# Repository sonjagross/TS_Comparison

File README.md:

# TS_Comparison
This repository includes all necessary code an description to build an experimental setup for the evaluation of tactile sensors.
- Overall description of the setup are provided in experimentalSetup/Bachelor_Thesis_ManuelKrummschmidt
- Necessary CAD files are provided in experimentalSetup/CADModels
- PCB and CAD Models of all Sensors are provided in sensorDesign/
- The code for the control of the robot setup is provided in code/RobotControl/
- A Tutorial on how to use the robot program code and include changes is provided in tutorials/

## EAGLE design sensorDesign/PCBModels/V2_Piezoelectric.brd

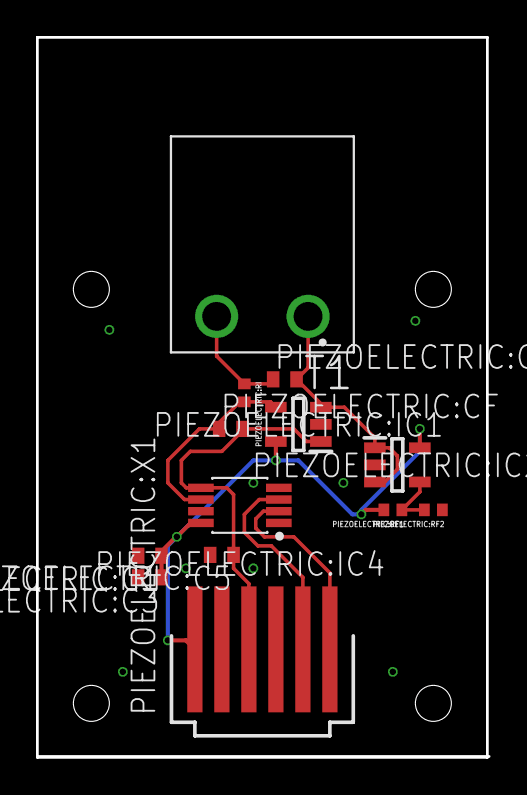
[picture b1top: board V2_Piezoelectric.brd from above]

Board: 2 copper layers, 25.0 x 40.0 mm, 13 parts (0 on the bottom side), 9 nets.

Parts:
PIEZOELECTRIC:C1, PIEZOELECTRIC:C5: GCM155R71C104JA55; C0402
PIEZOELECTRIC:C3: GCM155C7; C0402
PIEZOELECTRIC:CC: GCM155R71C104JA55; C0402
PIEZOELECTRIC:CF: GCM155R71C104JA55; C0402
PIEZOELECTRIC:IC1, PIEZOELECTRIC:IC2: TLV2771CDBVR; SOT95P280X145-5N
PIEZOELECTRIC:IC4: MCP4531-103E/MS; MSOP8
PIEZOELECTRIC:RF1, PIEZOELECTRIC:RF2: 10k; R0402
PIEZOELECTRIC:RI: 10k; R0402
PIEZOELECTRIC:X1: 87438-06
T1: 691312510002

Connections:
GND: PIEZOELECTRIC:C1.2, PIEZOELECTRIC:C3.2, PIEZOELECTRIC:C5.2, PIEZOELECTRIC:IC1.2, PIEZOELECTRIC:IC2.2, PIEZOELECTRIC:IC4.1, PIEZOELECTRIC:IC4.4, PIEZOELECTRIC:RF2.1, PIEZOELECTRIC:X1.2, PIEZOELECTRIC:X1.4
P+: PIEZOELECTRIC:CC.1, PIEZOELECTRIC:RI.1, T1.2
P-: PIEZOELECTRIC:CC.2, PIEZOELECTRIC:IC1.3, PIEZOELECTRIC:IC2.1, PIEZOELECTRIC:IC2.3, T1.1
PIEZOELECTRIC:IN-: PIEZOELECTRIC:CF.1, PIEZOELECTRIC:IC1.4, PIEZOELECTRIC:IC4.6, PIEZOELECTRIC:RI.2
PIEZOELECTRIC:N$3: PIEZOELECTRIC:IC2.4, PIEZOELECTRIC:RF1.1, PIEZOELECTRIC:RF2.2
PIEZOELECTRIC:OUT: PIEZOELECTRIC:C5.1, PIEZOELECTRIC:CF.2, PIEZOELECTRIC:IC1.1, PIEZOELECTRIC:IC4.5, PIEZOELECTRIC:X1.3
PIEZOELECTRIC:SCL: PIEZOELECTRIC:IC4.2, PIEZOELECTRIC:X1.6
PIEZOELECTRIC:SDA: PIEZOELECTRIC:IC4.3, PIEZOELECTRIC:X1.5
PIEZOELECTRIC:V+: PIEZOELECTRIC:C1.1, PIEZOELECTRIC:C3.1, PIEZOELECTRIC:IC1.5, PIEZOELECTRIC:IC2.5, PIEZOELECTRIC:IC4.8, PIEZOELECTRIC:RF1.2, PIEZOELECTRIC:X1.1

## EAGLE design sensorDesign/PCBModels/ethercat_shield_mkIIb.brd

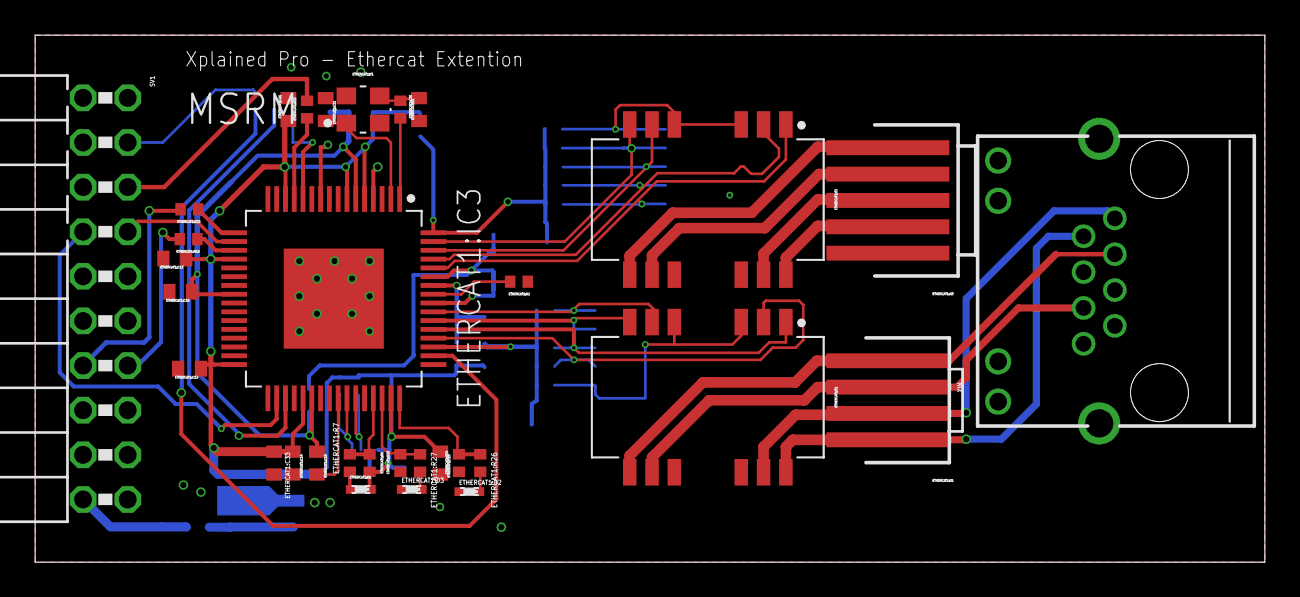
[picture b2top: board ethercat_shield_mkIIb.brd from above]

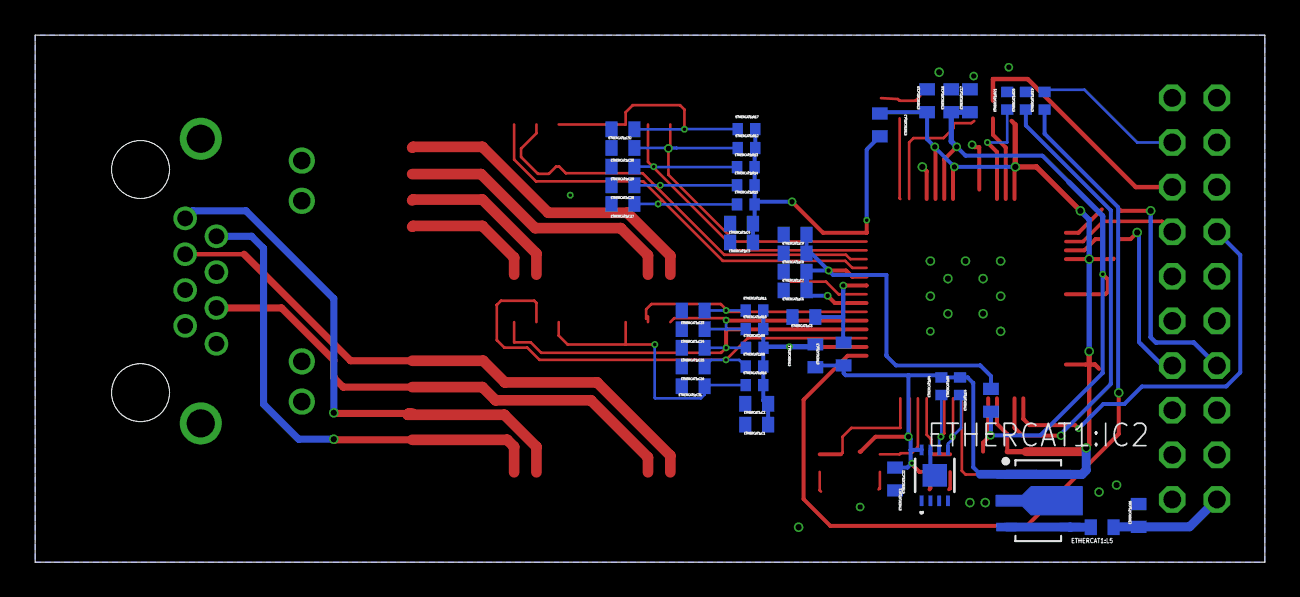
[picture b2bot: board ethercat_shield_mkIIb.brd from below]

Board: 2 copper layers, 70.0 x 30.0 mm, 78 parts (46 on the bottom side), 51 nets.

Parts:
ETHERCAT1:C1, ETHERCAT1:C3, ETHERCAT1:C6, ETHERCAT1:C8, ETHERCAT1:C16: 1u; C0402
ETHERCAT1:C2, ETHERCAT1:C4, ETHERCAT1:C5, ETHERCAT1:C7, ETHERCAT1:C9, ETHERCAT1:C10, ETHERCAT1:C11, ETHERCAT1:C12, ETHERCAT1:C13, ETHERCAT1:C14, ETHERCAT1:C15, ETHERCAT1:C18, ETHERCAT1:C19, ETHERCAT1:C22: 100n; C0402
ETHERCAT1:C17: 470p; C0402
ETHERCAT1:C20, ETHERCAT1:C21: 18p; C0402
ETHERCAT1:C23, ETHERCAT1:C24, ETHERCAT1:C25, ETHERCAT1:C26, ETHERCAT1:C27, ETHERCAT1:C28, ETHERCAT1:C29, ETHERCAT1:C30: GCM1555C1H100JA16; C0402
ETHERCAT1:C31, ETHERCAT1:C32: 22n; C0402
ETHERCAT1:C33: GRM155C80J106ME11D; C0402
ETHERCAT1:C66: 1uF; C0402
ETHERCAT1:D1, ETHERCAT1:D2, ETHERCAT1:D3: QBLP595-IG; LED0402
ETHERCAT1:IC1: CAT24C512IGT3HU5; UDFN8
ETHERCAT1:IC2: RP115H331B-T1-FE; SOT-89-5
ETHERCAT1:IC3: LAN9252/PT; TQFP64-T570
ETHERCAT1:L1, ETHERCAT1:L2, ETHERCAT1:L3, ETHERCAT1:L4, ETHERCAT1:L5: BLM15EG221SH1D; BEAD0402
ETHERCAT1:R1, ETHERCAT1:R16, ETHERCAT1:R17: 0R; R0402
ETHERCAT1:R2: 12k1; R0402
ETHERCAT1:R4, ETHERCAT1:R5: 4k7; R0402
ETHERCAT1:R6, ETHERCAT1:R24, ETHERCAT1:R25: 10k; R0402
ETHERCAT1:R7, ETHERCAT1:R26, ETHERCAT1:R27: RL0402FR-7W10KL; R0402
ETHERCAT1:R8, ETHERCAT1:R9, ETHERCAT1:R10, ETHERCAT1:R11, ETHERCAT1:R12, ETHERCAT1:R13, ETHERCAT1:R14, ETHERCAT1:R15: 49R9; R0402
ETHERCAT1:R18, ETHERCAT1:R19, ETHERCAT1:R20, ETHERCAT1:R21, ETHERCAT1:R22, ETHERCAT1:R23: 100; R0402
ETHERCAT1:T1, ETHERCAT1:T2: 749020100; SOIC127P965X533-16-TRAFO
ETHERCAT1:X1: 87438-0443; 87438-04
ETHERCAT1:X3: 87438-0543; 87438-05
ETHERCAT1:Y1: ECX-2236
SV1: FE10-2W
XIN: ATJ34L; J1

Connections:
+5V: ETHERCAT1:C66.1, ETHERCAT1:L5.1, SV1.20
ECAT_CS: ETHERCAT1:R19.2, SV1.3
ECAT_MISO: ETHERCAT1:R22.2, SV1.5
ECAT_MOSI: ETHERCAT1:R23.2, SV1.14
ECAT_SCK: ETHERCAT1:R18.2, SV1.13
ETHERCAT1:#MISO: ETHERCAT1:IC3.13, ETHERCAT1:R22.1
ETHERCAT1:#MOSI: ETHERCAT1:IC3.17, ETHERCAT1:R23.1
ETHERCAT1:#SCK: ETHERCAT1:IC3.19, ETHERCAT1:R18.1
ETHERCAT1:#SCS#: ETHERCAT1:IC3.50, ETHERCAT1:R19.1
ETHERCAT1:#SQI2: ETHERCAT1:IC3.12, ETHERCAT1:R21.1
ETHERCAT1:#SQI3: ETHERCAT1:IC3.35, ETHERCAT1:R20.1
ETHERCAT1:+3V3: ETHERCAT1:C10.1, ETHERCAT1:C11.1, ETHERCAT1:C12.1, ETHERCAT1:C13.1, ETHERCAT1:C14.1, ETHERCAT1:C15.1, ETHERCAT1:C22.1, ETHERCAT1:C33.1, ETHERCAT1:D1.2, ETHERCAT1:IC1.8, ETHERCAT1:IC2.1, ETHERCAT1:IC2.5, ETHERCAT1:IC3.5, ETHERCAT1:IC3.7, ETHERCAT1:IC3.14, ETHERCAT1:IC3.20, ETHERCAT1:IC3.32, ETHERCAT1:IC3.37, ETHERCAT1:IC3.47, ETHERCAT1:L1.1, ETHERCAT1:L2.1, ETHERCAT1:L3.1, ETHERCAT1:R4.2, ETHERCAT1:R5.2, ETHERCAT1:R6.2
ETHERCAT1:CT1: ETHERCAT1:C31.1, ETHERCAT1:R16.1, ETHERCAT1:T1.3, ETHERCAT1:T1.6
ETHERCAT1:CT2: ETHERCAT1:C32.1, ETHERCAT1:R17.1, ETHERCAT1:T2.3, ETHERCAT1:T2.6
ETHERCAT1:GPIO0: ETHERCAT1:IC3.48, ETHERCAT1:R24.2, ETHERCAT1:R26.1
ETHERCAT1:GPIO1: ETHERCAT1:IC3.46, ETHERCAT1:R25.2, ETHERCAT1:R27.1
ETHERCAT1:GPIO2: ETHERCAT1:IC3.45, ETHERCAT1:R6.1, ETHERCAT1:R7.2
ETHERCAT1:I2C_SCL: ETHERCAT1:IC1.6, ETHERCAT1:IC3.43, ETHERCAT1:R4.1
ETHERCAT1:I2C_SDA: ETHERCAT1:IC1.5, ETHERCAT1:IC3.42, ETHERCAT1:R5.1
ETHERCAT1:N$1: ETHERCAT1:D2.2, ETHERCAT1:R26.2
ETHERCAT1:N$2: ETHERCAT1:D3.2, ETHERCAT1:R27.2
ETHERCAT1:N$3: ETHERCAT1:IC2.3, ETHERCAT1:IC2.4, ETHERCAT1:L5.2
ETHERCAT1:N$15: ETHERCAT1:D1.1, ETHERCAT1:R7.1
ETHERCAT1:OSCI: ETHERCAT1:IC3.1, ETHERCAT1:R1.2
ETHERCAT1:OSCI1: ETHERCAT1:C20.2, ETHERCAT1:R1.1, ETHERCAT1:Y1.3
ETHERCAT1:OSCO: ETHERCAT1:C21.2, ETHERCAT1:IC3.2, ETHERCAT1:Y1.1
ETHERCAT1:OUT_RX_N: ETHERCAT1:T2.9, ETHERCAT1:X3.5
ETHERCAT1:OUT_RX_P: ETHERCAT1:T2.10, ETHERCAT1:X3.4
ETHERCAT1:OUT_TX_N: ETHERCAT1:T2.15, ETHERCAT1:X3.3
ETHERCAT1:OUT_TX_P: ETHERCAT1:T2.16, ETHERCAT1:X3.2
ETHERCAT1:RBIAS: ETHERCAT1:IC3.57, ETHERCAT1:R2.2
ETHERCAT1:RXA_N: ETHERCAT1:C24.1, ETHERCAT1:IC3.54, ETHERCAT1:R10.1, ETHERCAT1:T1.8
ETHERCAT1:RXA_P: ETHERCAT1:C23.1, ETHERCAT1:IC3.55, ETHERCAT1:R11.1, ETHERCAT1:T1.7
ETHERCAT1:RXB_N: ETHERCAT1:C28.1, ETHERCAT1:IC3.61, ETHERCAT1:R14.1, ETHERCAT1:T2.2
ETHERCAT1:RXB_P: ETHERCAT1:C27.1, ETHERCAT1:IC3.60, ETHERCAT1:R15.1, ETHERCAT1:T2.1
ETHERCAT1:TXA_N: ETHERCAT1:C26.1, ETHERCAT1:IC3.52, ETHERCAT1:R8.1, ETHERCAT1:T1.2
ETHERCAT1:TXA_P: ETHERCAT1:C25.1, ETHERCAT1:IC3.53, ETHERCAT1:R9.1, ETHERCAT1:T1.1
ETHERCAT1:TXB_N: ETHERCAT1:C30.1, ETHERCAT1:IC3.63, ETHERCAT1:R12.1, ETHERCAT1:T2.8
ETHERCAT1:TXB_P: ETHERCAT1:C29.1, ETHERCAT1:IC3.62, ETHERCAT1:R13.1, ETHERCAT1:T2.7
ETHERCAT1:VDD: ETHERCAT1:C16.1, ETHERCAT1:C17.1, ETHERCAT1:C18.1, ETHERCAT1:C19.1, ETHERCAT1:IC3.6, ETHERCAT1:IC3.24, ETHERCAT1:IC3.38, ETHERCAT1:L4.1
ETHERCAT1:VDD12TX: ETHERCAT1:C6.1, ETHERCAT1:C7.1, ETHERCAT1:C8.1, ETHERCAT1:C9.1, ETHERCAT1:IC3.56, ETHERCAT1:IC3.59, ETHERCAT1:L4.2
ETHERCAT1:VDD33BIAS: ETHERCAT1:C5.1, ETHERCAT1:IC3.58, ETHERCAT1:L3.2
ETHERCAT1:VDD33TXRX1: ETHERCAT1:C1.1, ETHERCAT1:C2.1, ETHERCAT1:IC3.51, ETHERCAT1:L1.2, ETHERCAT1:R8.2, ETHERCAT1:R9.2, ETHERCAT1:R10.2, ETHERCAT1:R11.2, ETHERCAT1:R16.2
ETHERCAT1:VDD33TXRX2: ETHERCAT1:C3.1, ETHERCAT1:C4.1, ETHERCAT1:IC3.64, ETHERCAT1:L2.2, ETHERCAT1:R12.2, ETHERCAT1:R13.2, ETHERCAT1:R14.2, ETHERCAT1:R15.2, ETHERCAT1:R17.2
GND: ETHERCAT1:C1.2, ETHERCAT1:C2.2, ETHERCAT1:C3.2, ETHERCAT1:C4.2, ETHERCAT1:C5.2, ETHERCAT1:C6.2, ETHERCAT1:C7.2, ETHERCAT1:C8.2, ETHERCAT1:C9.2, ETHERCAT1:C10.2, ETHERCAT1:C11.2, ETHERCAT1:C12.2, ETHERCAT1:C13.2, ETHERCAT1:C14.2, ETHERCAT1:C15.2, ETHERCAT1:C16.2, ETHERCAT1:C17.2, ETHERCAT1:C18.2, ETHERCAT1:C19.2, ETHERCAT1:C20.1, ETHERCAT1:C21.1, ETHERCAT1:C22.2, ETHERCAT1:C23.2, ETHERCAT1:C24.2, ETHERCAT1:C25.2, ETHERCAT1:C26.2, ETHERCAT1:C27.2, ETHERCAT1:C28.2, ETHERCAT1:C29.2, ETHERCAT1:C30.2, ETHERCAT1:C31.2, ETHERCAT1:C32.2, ETHERCAT1:C33.2, ETHERCAT1:C66.2, ETHERCAT1:D2.1, ETHERCAT1:D3.1, ETHERCAT1:IC1.1, ETHERCAT1:IC1.2, ETHERCAT1:IC1.3, ETHERCAT1:IC1.4, ETHERCAT1:IC1.7, ETHERCAT1:IC1.9, ETHERCAT1:IC2.2, ETHERCAT1:IC3.4, ETHERCAT1:IC3.8, ETHERCAT1:IC3.9, ETHERCAT1:IC3.10, ETHERCAT1:IC3.41, ETHERCAT1:IC3.65, ETHERCAT1:R2.1, ETHERCAT1:R24.1, ETHERCAT1:R25.1, ETHERCAT1:Y1.2, ETHERCAT1:Y1.4, SV1.2, SV1.19
RA_N: ETHERCAT1:T1.9, ETHERCAT1:X1.4, XIN.3
RA_P: ETHERCAT1:T1.10, ETHERCAT1:X1.3, XIN.6
SYNC0: ETHERCAT1:IC3.34, SV1.8
SYNC1: ETHERCAT1:IC3.18, SV1.7
TA_N: ETHERCAT1:T1.15, ETHERCAT1:X1.2, XIN.1
TA_P: ETHERCAT1:T1.16, ETHERCAT1:X1.1, XIN.2

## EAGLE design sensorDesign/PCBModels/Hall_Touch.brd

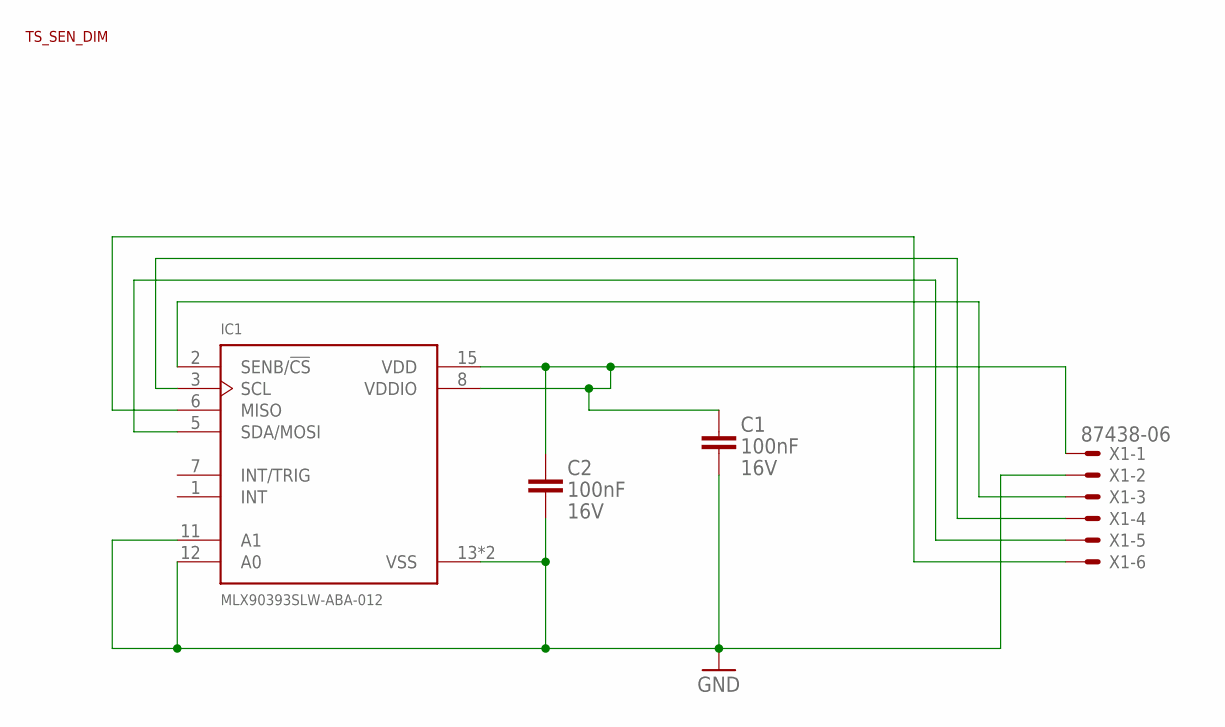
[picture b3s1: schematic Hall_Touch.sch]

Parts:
C1, C2: GCM155R71C104JA55; C0402
DIMENSION1: TS_SEN_DIM; SEN_DIM
IC1: MLX90393SLW-ABA-012; QFN50P300X300X100-17T180N
X1: 87438-06

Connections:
GND: C1.2, C2.2, IC1.11 (A1), IC1.12 (A0), IC1.13 (VSS), IC1.17 (VSS), X1.2
unnamed: IC1.2 (SENB/!CS), X1.3
unnamed: C1.1, C2.1, IC1.8 (VDDIO), IC1.15 (VDD), X1.1
unnamed: IC1.5 (SDA/MOSI), X1.5
unnamed: IC1.6 (MISO), X1.6
unnamed: IC1.3 (SCL), X1.4

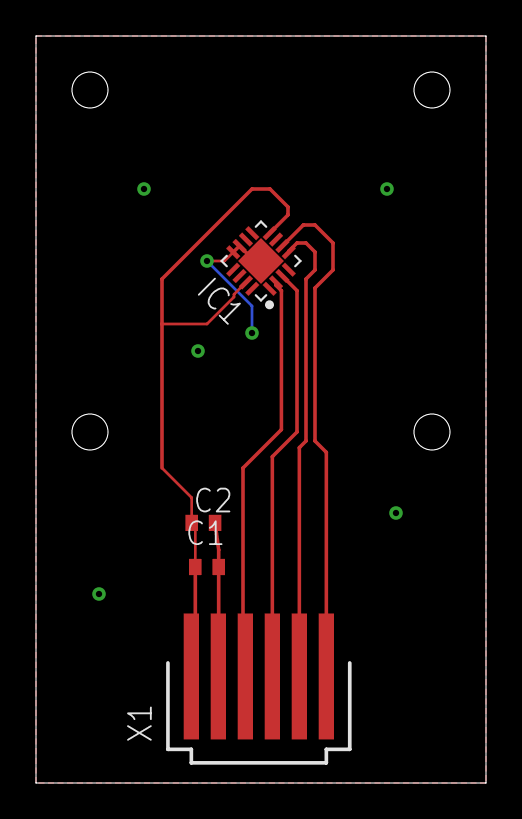
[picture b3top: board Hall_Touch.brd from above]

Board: 2 copper layers, 25.0 x 41.5 mm, 5 parts (0 on the bottom side), 6 nets.

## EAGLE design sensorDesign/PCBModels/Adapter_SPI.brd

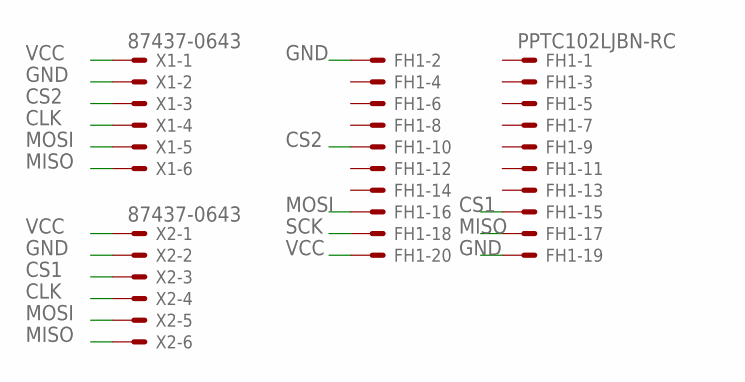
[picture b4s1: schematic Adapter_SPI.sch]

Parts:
FH1: PPTC102LJBN-RC; S5524-ND
X1, X2: 87437-0643; 87437-06

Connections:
CLK: X1.4, X2.4
CS1: FH1.P$15, X2.3
CS2: FH1.P$10, X1.3
GND: FH1.P$2, FH1.P$19, X1.2, X2.2
MISO: FH1.P$17, X1.6, X2.6
MOSI: FH1.P$16, X1.5, X2.5
SCK: FH1.P$18
VCC: FH1.P$20, X1.1, X2.1

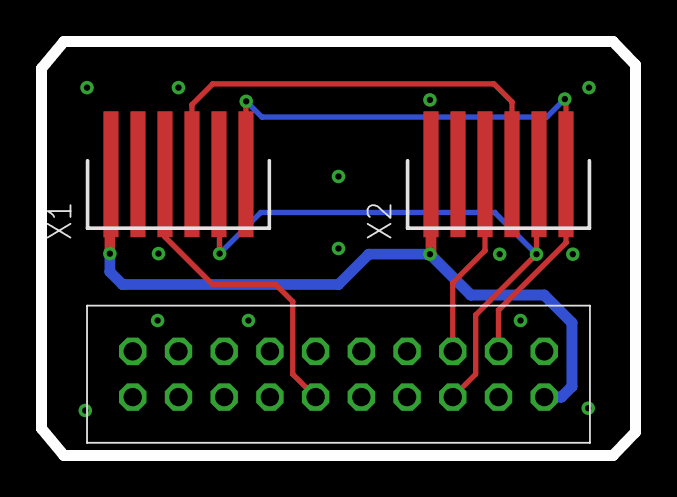
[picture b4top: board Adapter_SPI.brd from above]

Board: 2 copper layers, 33.0 x 23.0 mm, 3 parts (0 on the bottom side), 7 nets.

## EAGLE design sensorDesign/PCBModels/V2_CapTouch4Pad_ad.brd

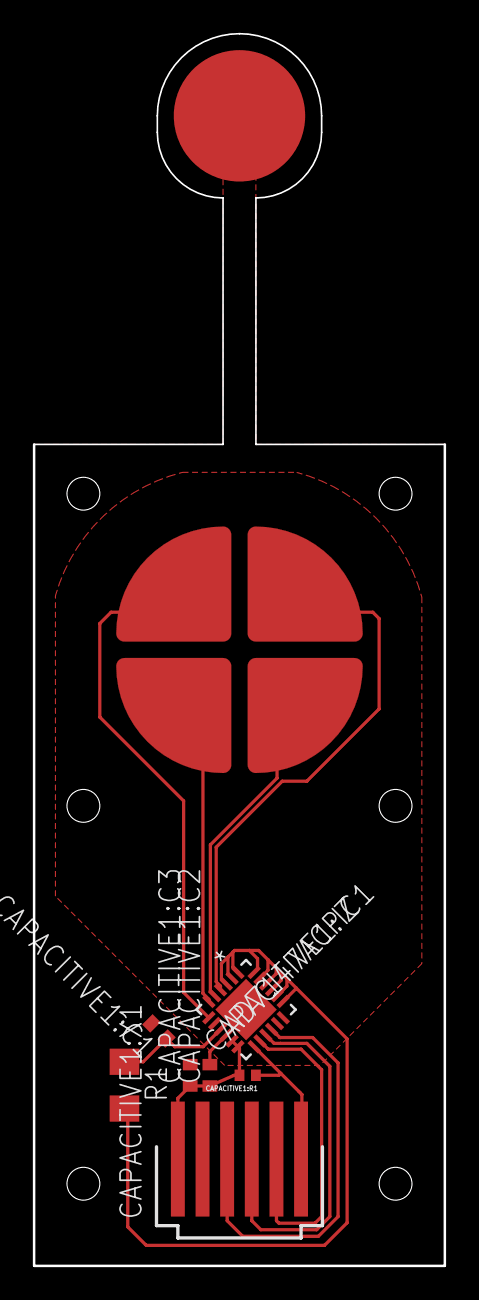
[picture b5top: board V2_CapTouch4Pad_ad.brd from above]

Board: 2 copper layers, 25.0 x 75.0 mm, 12 parts (0 on the bottom side), 12 nets.

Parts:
CAPACITIVE1:C1, CAPACITIVE1:C2: GCM155R71C104JA55; C0402
CAPACITIVE1:C3: GCM155C7; C0402
CAPACITIVE1:IC1: AD7147ACPZ; CP_24_3_ADI-M
CAPACITIVE1:R1: RT0402FRE074K7L; R0402
CAPACITIVE1:X1: 87438-06
PAD_LOWLEFT: TS_ELECTRODE-SLICE-BACKUP2; TS_ELECTRODE-SLICE
PAD_LOWRIGHT: TS_ELECTRODE-SLICE-BACKUP2; TS_ELECTRODE-SLICE
PAD_TOP_LEFT: TS_ELECTRODE-SLICE-BACKUP2; TS_ELECTRODE-SLICE
PAD_TOP_RIGHT: TS_ELECTRODE-SLICE-BACKUP2; TS_ELECTRODE-SLICE
R1: RL1206FR-7W0R1L; R1206
U$5: TS_ELECTRODE_CIRC

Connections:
CAPACITIVE1:N$1: CAPACITIVE1:IC1.13, CAPACITIVE1:R1.1, CAPACITIVE1:X1.6
CAPACITIVE1:N$8: CAPACITIVE1:IC1.16, CAPACITIVE1:X1.3
CAPACITIVE1:N$9: CAPACITIVE1:IC1.15, CAPACITIVE1:X1.4
CAPACITIVE1:N$10: CAPACITIVE1:IC1.14, CAPACITIVE1:X1.5
CAPACITIVE1:VCC: CAPACITIVE1:C2.1, CAPACITIVE1:C3.1, CAPACITIVE1:IC1.11, CAPACITIVE1:IC1.12, CAPACITIVE1:R1.2, CAPACITIVE1:X1.1
GND: CAPACITIVE1:C1.2, CAPACITIVE1:C2.2, CAPACITIVE1:C3.2, CAPACITIVE1:IC1.10, CAPACITIVE1:IC1.HTAB, CAPACITIVE1:X1.2, U$5.0
unnamed: CAPACITIVE1:IC1.4, PAD_TOP_RIGHT.PAD$1
unnamed: CAPACITIVE1:IC1.5, PAD_LOWRIGHT.PAD$1
unnamed: CAPACITIVE1:IC1.6, PAD_LOWLEFT.PAD$1
unnamed: CAPACITIVE1:IC1.7, PAD_TOP_LEFT.PAD$1
unnamed: CAPACITIVE1:IC1.1, CAPACITIVE1:IC1.2, CAPACITIVE1:IC1.3, CAPACITIVE1:IC1.19, CAPACITIVE1:IC1.20, CAPACITIVE1:IC1.21, CAPACITIVE1:IC1.22, CAPACITIVE1:IC1.23, CAPACITIVE1:IC1.24, R1.2
unnamed: CAPACITIVE1:C1.1, CAPACITIVE1:IC1.9, R1.1

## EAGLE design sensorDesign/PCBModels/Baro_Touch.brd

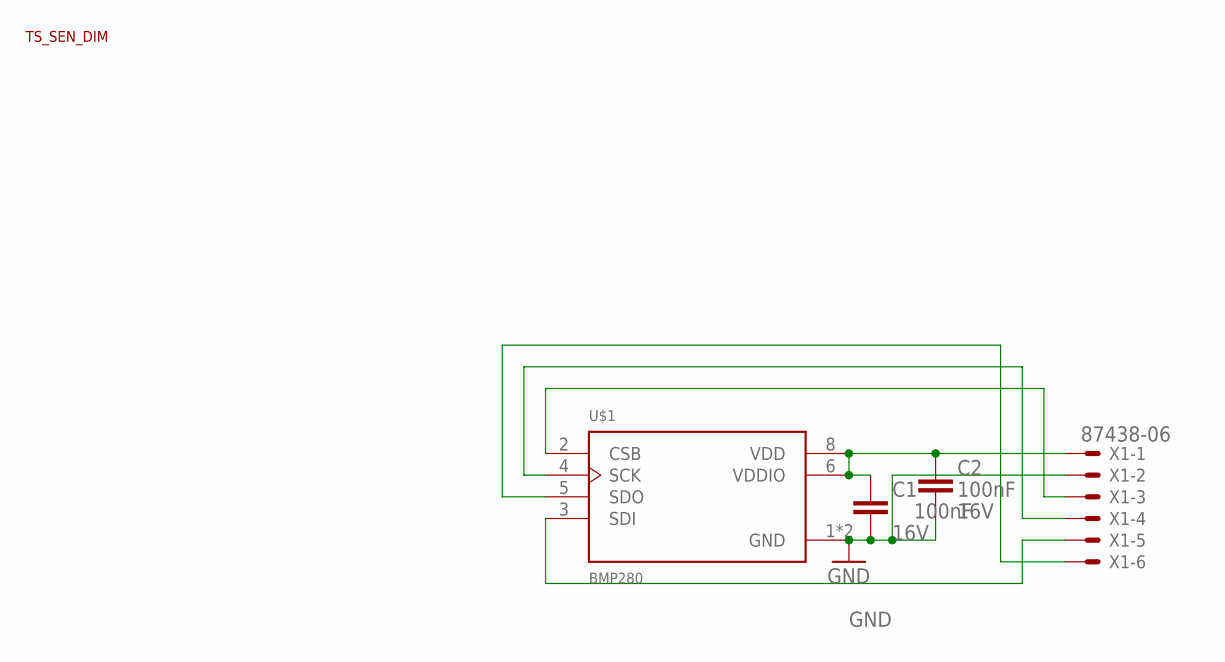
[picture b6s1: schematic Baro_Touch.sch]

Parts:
C1, C2: GCM155R71C104JA55; C0402
DIMENSION1: TS_SEN_DIM; SEN_DIM
U$1: BMP280; 8-SMD
X1: 87438-06

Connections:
GND: C1.2, C2.2, U$1.1 (GND), U$1.7 (GND), X1.2
unnamed: C1.1, C2.1, U$1.6 (VDDIO), U$1.8 (VDD), X1.1
unnamed: U$1.2 (CSB), X1.3
unnamed: U$1.4 (SCK), X1.4
unnamed: U$1.5 (SDO), X1.6
unnamed: U$1.3 (SDI), X1.5

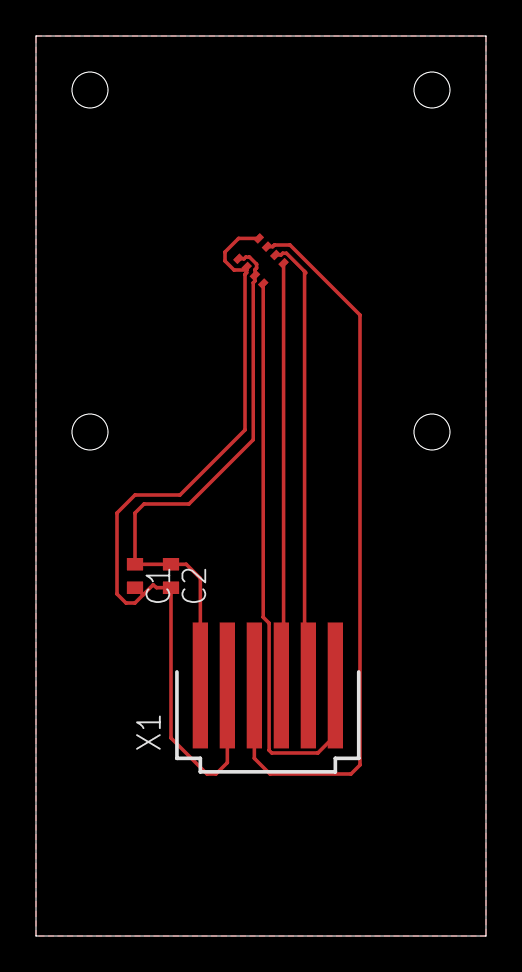
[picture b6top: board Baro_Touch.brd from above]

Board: 2 copper layers, 25.0 x 50.0 mm, 5 parts (0 on the bottom side), 6 nets.

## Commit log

2022-02-22 Initial commit of code, CAD and PCBs
2022-05-31 initial commit Robot Control, changes AtmelStudio
    Initial commit robot control and changes to IC programming parameters in Atmel Studio
2022-06-04 Add python experiment scripts
2022-06-04 Add CAD models for experimental setup
2025-02-27 Add Description
